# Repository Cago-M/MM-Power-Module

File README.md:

# MM-Power-Module

This repository contains the complete design files, documentation, and output artifacts of the Power Subsystem used in a micro-mouse robot. It includes USB-C power negotiation, multi-rail regulation, Li-ion battery support, and load switching for motors and auxiliary peripherals

#### Repository Contents
| Folder/File      | Description                                                                    |
| ---------------- | ------------------------------------------------------------------------------ |
| `kicad_project/` | Full KiCad 8+ project files (`.kicad_sch`, `.kicad_pcb`, symbols, footprints). |
| `gerber/`        | Gerber files for PCB manufacturing (RS-274X standa.                         |
| `bom/`           | Bill of Materials in `.csv` and `.xlsx` formats.                               |
| `csv_exports/`   | CSV exports of netlist, components, positions for assembly.                    |
| `images/`        | High-res renderings of the board (3D view, top view, bottom view).             |
| `README.md`      | You're reading it.                                                             |

## Subsystem Overview
The power subsystem fulfills the following requirements:
- Provide 5V and 3V3 regulated rails to sensors, MCU, and logic.
- Interface with USB-C input and negotiate 9V via CH224K.
- Support auxiliary laods via two TPS22929D load switches.
- Power four DC motors via DRV8833 motor drivers.

#### Key Components
| Component      | Function                          |
| -------------- | --------------------------------- |
| CH224K         | USB-C PD negotiation (9 V out)    |
| LM296T-5       | 5 V linear regulator              |
| AMS1117-3.3    | 3.3 V LDO regulator               |
| TP4056         | Li-ion charger (w/ protection)    |
| DRV8833        | Dual H-bridge motor drivers       |
| TPS22929D      | Load switches for aux peripherals |
| INA219         | Current sensing (I²C telemetry)   |

#### Board Previews

## License
This project is released under the MIT License. Attribution is appreciated if reused or modified.

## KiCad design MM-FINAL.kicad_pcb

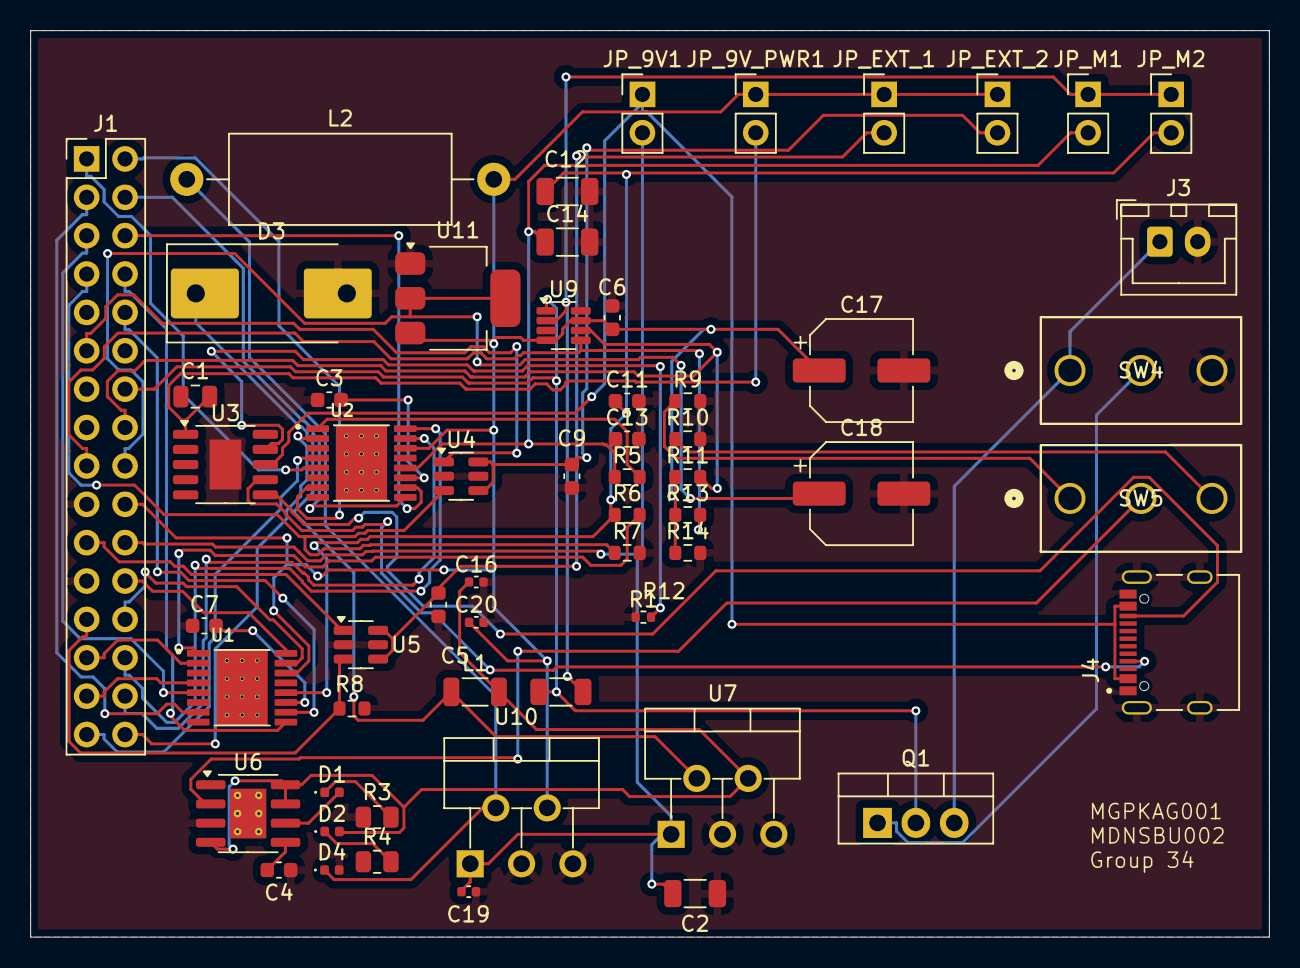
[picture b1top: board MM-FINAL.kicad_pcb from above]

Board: 2 copper layers, 82.0 x 60.0 mm, 58 parts (0 on the bottom side), 53 nets.

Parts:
C1: 1u; C_0805_2012Metric
C2: 100u; C_1206_3216Metric
C3, C7: C_Small (0.1uF); C_0603_1608Metric
C4: 220u; C_0603_1608Metric
C5, C6, C9: 1u; C_0603_1608Metric
C11, C13: 0.1u; C_0603_1608Metric
C12, C14: 10u; C_1206_3216Metric
C16, C20: 10u; C_0402_1005Metric
C17, C18: 10u; CP_Elec_6.3x5.4
C19: 47u; C_0402_1005Metric
D1, D2: LED; LED_0402_1005Metric
D3: 1N5822; D_SMC-RM10_Universal_Handsoldering
D4: D_Zener; D_0402_1005Metric
J1: Conn_02x16_Odd_Even; PinHeader_2x16_P2.54mm_Vertical
J3: Conn_01x02; JST_XH_B2B-XH-A_1x02_P2.50mm_Vertical
J4: TYPE-C-31-M-12; HRO_TYPE-C-31-M-12
JP_9V1, JP_9V_PWR1: Conn_01x02; PinHeader_1x02_P2.54mm_Vertical
JP_EXT_1, JP_EXT_2: Conn_01x02; PinHeader_1x02_P2.54mm_Vertical
JP_M1, JP_M2: Conn_01x02; PinHeader_1x02_P2.54mm_Vertical
L1: 100u; L_1206_3216Metric
L2: 40u; L_Axial_L14.5mm_D5.8mm_P20.32mm_Horizontal_Fastron_HBCC
Q1: IRF9540N; TO-220-3_Vertical
R1: 6.8k; R_0402_1005Metric
R3, R4: 1k; R_0805_2012Metric
R5, R6, R7, R8, R11, R13, R14: 10k; R_0603_1608Metric
R9: 5k; R_0603_1608Metric
R10: 1.67k; R_0603_1608Metric
R12: 0.1; R_1206_3216Metric
SW4, SW5: SS-12D10G5; SS-12D10G5_XKB
U1, U2: DRV8833PWP; IC_DRV8833PWP
U3: CH224K; SSOP-10-1EP_3.9x4.9mm_P1mm_EP2.1x3.3mm
U4, U5: TPS22929D; SOT-23-6
U6: TP4056-42-ESOP8; SOIC-8-1EP_3.9x4.9mm_P1.27mm_EP2.41x3.3mm_ThermalVias
U7, U10: LM2596T-5; TO-220-5_P3.4x3.7mm_StaggerOdd_Lead3.8mm_Vertical
U9: INA219AxDCN; SOT-23-8
U11: AMS1117-3.3; SOT-223-3_TabPin2

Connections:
3V3 Out: C18.1, J1.18, U11.2 (VO)
5V Out: C6.2, C17.1, C20.1, J1.20, JP_9V_PWR1.1, JP_EXT_1.1, JP_EXT_2.1, L2.2, R11.1, R13.1, R14.1, U1.14 (VINT), U2.14 (VINT), U9.4 (VS), U9.7 (A0), U10.4 (FB), U11.3 (VI)
+BATT: J1.14, Q1.2 (D), R12.1, U9.1 (IN+)
+BATT_out: JP_M1.1, JP_M2.1, R12.2, U9.2 (IN-)
CTRL_EXT_LOAD1: J1.25, R8.1, U5.3 (ON)
CTRL_EXT_LOAD2: J1.7, R7.1, U4.3 (ON)
EXT_LOAD1_OUT: J1.21, U5.1 (VOUT)
EXT_LOAD2_OUT: J1.11, U4.1 (VOUT)
GND: C1.1, C2.2, C3.1, C4.2, C5.2, C6.1, C7.1, C9.2, C11.2, C12.2, C13.2, C14.2, C16.2, C17.2, C18.2, C19.2, C20.2, D3.2 (A), D4.2 (A), J1.19, J1.23, J3.2, J4.A1_B12 (GND), J4.B1_A12 (GND), J4.S1 (SHIELD), J4.S2 (SHIELD), J4.S3 (SHIELD), J4.S4 (SHIELD), R1.1, R3.1, R4.1, R7.2, R8.2, R9.2, R10.2, R14.2, SW4.3 (C), U1.3 (AISEN), U1.6 (BISEN), U1.13 (GND), U1.17 (GND), U2.3 (AISEN), U2.6 (BISEN), U2.13 (GND), U2.17 (GND), U3.11 (GND), U4.2 (GND), U4.5 (GND), U5.2 (GND), U5.5 (GND), U6.1 (TEMP), U6.3 (GND), U7.3 (GND), U7.5 (~ON/OFF), U9.3 (GND), U9.8 (A1), U10.3 (GND), U10.5 (~ON/OFF), U11.1 (GND)
High Voltage (9V): C2.1, C19.1, J1.22, JP_9V1.2, U7.1 (VIN), U10.1 (VIN)
I2C1_SCL: J1.16, R11.2, U9.6 (SDA)
I2C1_SDA: J1.17, R13.2, U9.5 (SCL)
LiPo +ve: C4.1, U6.5 (BAT)
MOTOR1_A_OUT: J1.32, U2.2 (AOUT1)
MOTOR1_B_OUT: J1.31, U2.4 (AOUT2)
MOTOR2_A_OUT: J1.2, U2.7 (BOUT1)
MOTOR2_B_OUT: J1.1, U2.5 (BOUT2)
MOTOR2_CTRL1: J1.4, U2.9 (BIN1)
MOTOR2_CTRL2: J1.6, U2.10 (BIN2)
MOTOR3_A_OUT: J1.27, U1.2 (AOUT1)
MOTOR3_B_OUT: J1.29, U1.4 (AOUT2)
MOTOR3_CTRL1: J1.24, U1.16 (AIN1)
MOTOR3_CTRL2: J1.26, U1.15 (AIN2)
MOTOR4_CTRL1: J1.8, U1.9 (BIN1)
MOTOR4_CTRL2: J1.10, U1.10 (BIN2)
Motor1_CTRL1: J1.28, U2.16 (AIN1)
Motor1_CTRL2: J1.30, U2.15 (AIN2)
Motor4_A_OUT: J1.3, U1.7 (BOUT1)
Motor4_B_OUT: J1.5, U1.5 (BOUT2)
unnamed: D1.2 (A), U6.6 (~STDBY)
unnamed: D1.1 (K), R3.2
unnamed: C16.1, D2.2 (A), L1.2, U6.4 (V_{CC}), U6.7 (~CHRG), U6.8 (CE), U7.4 (FB)
unnamed: D2.1 (K), R4.2
unnamed: D3.1 (K), L1.1, U7.2 (OUT)
unnamed: D4.1 (K), L2.1, U10.2 (OUT)
unnamed: J4.A5 (CC1), U3.7 (CC1)
unnamed: J4.B5 (CC2), U3.6 (CC2)
unnamed: J4.A4_B9 (VBUS), J4.B4_A9 (VBUS), JP_9V1.1, U3.8 (VBUS)
unnamed: C1.2, JP_9V_PWR1.2, U3.1 (VDD)
unnamed: C5.1, JP_EXT_1.2, U5.4 (VIN), U5.6 (VIN)
unnamed: C9.1, JP_EXT_2.2, U4.4 (VIN), U4.6 (VIN)
unnamed: C13.1, C14.1, JP_M1.2, R5.1, U2.12 (VM)
unnamed: C11.1, C12.1, JP_M2.2, R6.1, U1.12 (VM)
unnamed: Q1.1 (G), SW4.2 (B)
unnamed: R9.1, SW5.1 (A)
unnamed: SW5.2 (B), U6.2 (PROG)
unnamed: R10.1, SW5.3 (C)
unnamed: C7.2, U1.11 (VCP)
unnamed: R6.2, U1.1 (~SLEEP)
unnamed: C3.2, U2.11 (VCP)
unnamed: R5.2, U2.1 (~SLEEP)
unnamed: R1.2, U3.9 (CFG1)
VBAT+: J3.1, Q1.3 (S), SW4.1 (A)

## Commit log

2025-05-16 Update README.md
    Initial readme.md, missing direct links to file projects & board images.
2025-05-16 kicad_project_files
